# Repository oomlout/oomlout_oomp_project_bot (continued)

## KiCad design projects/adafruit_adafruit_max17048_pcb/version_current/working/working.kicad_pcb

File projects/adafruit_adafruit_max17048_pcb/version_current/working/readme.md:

# OOMP Project  
## Adafruit-MAX17048-PCB  by adafruit  
  
oomp key: oomp_projects_flat_adafruit_adafruit_max17048_pcb  
(snippet of original readme)  
  
-- Adafruit MAX17048 LiPoly / LiIon Fuel Gauge and Battery Monitor PCB  
  
<a href="http://www.adafruit.com/products/5580"><br/>  
Click here to purchase one from the Adafruit shop</a>  
  
PCB files for the Adafruit MAX17048 LiPoly / LiIon Fuel Gauge and Battery Monitor.   
  
Format is EagleCAD schematic and board layout  
* https://www.adafruit.com/product/5580  
  
--- Description  
  
Low cost Lithium Polymer batteries have revolutionized electronics - they're thin, they're light, they can be regulated down to 3.3V and they're easy to charge. On your phone, there's a little image of a battery cell that tells you the percentage of charge - so you know when you absolutely need to plug it in and when you can stay untethered.  
  
The Adafruit MAX17048 LiPoly / LiIon Fuel Gauge and Battery Monitor does the same thing. Connect it to your Lipoly or LiIon battery and it will let you know the voltage of the cell, it does the annoying math of decoding the non-linear voltage to get you a valid percentage as well!  
  
Since this nice chip is I2C, it works with any and all microcontroller or microcomputer boards, from the Arduino UNO up to the Raspberry Pi. And you don't have to worry about logic level, as the gauge runs with 3.3V or 5.0V power and logic equally fine.  
  
To use, connect a 1S 3.7-4.2V Lithium Ion or Polymer battery to one of the JST 2 PH ports (either one). Then use the included JST PH jumper cable to connect to your boost converter, Feather, whatev  
  full source readme at [readme_src.md](readme_src.md)  
  
source repo at: [https://github.com/adafruit/Adafruit-MAX17048-PCB](https://github.com/adafruit/Adafruit-MAX17048-PCB)  
## Board  

## Schematic  

[schematic pdf](working_schematic.pdf)  
## Images

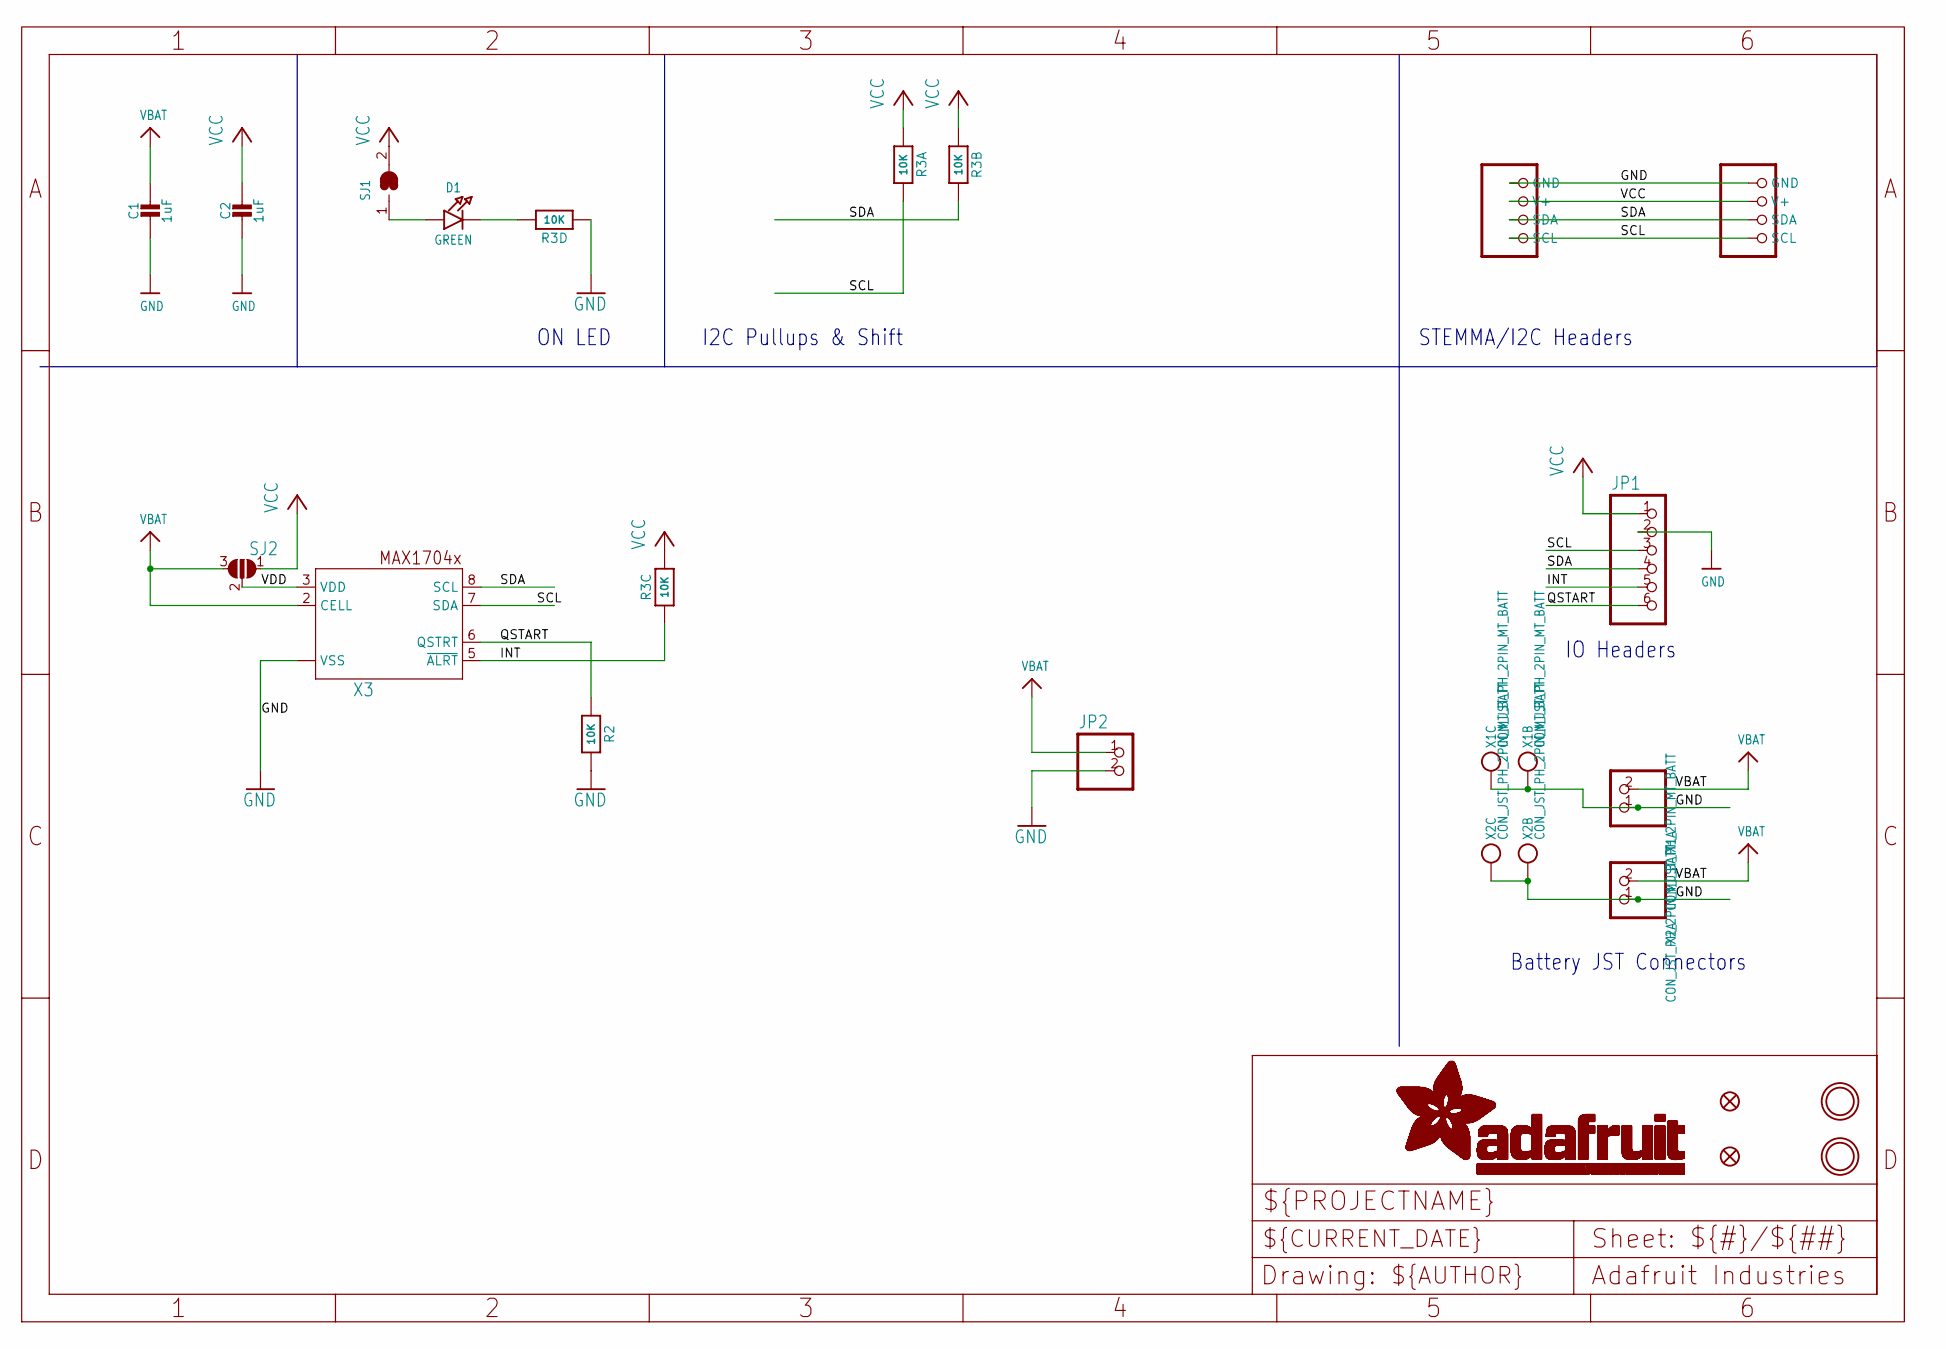
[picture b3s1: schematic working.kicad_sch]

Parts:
C1, C2: 1uF; 0603-NO
CONN3, CONN4: STEMMA_I2C_QT; JST_SH4
D1: GREEN; CHIPLED_0603_NOOUTLINE
FID3, FID4: FIDUCIAL_1MM
JP1: HEADER-1X670MIL; 1X06_ROUND_70
JP2: HEADER-1X2ROUND; 1X02_ROUND
R2: 10K; 0603-NO
R3: 10K; RESPACK_4X0603
SJ1: SOLDERJUMPERCLOSED; SOLDERJUMPER_CLOSEDWIRE
SJ2: SOLDERJUMPER_2WAY; SOLDERJUMPER_2WAY_OPEN_NOPASTE
U$19, U$21: MOUNTINGHOLE2.5; MOUNTINGHOLE_2.5_PLATED
X1, X2: CON_JST_PH_2PIN_MT_BATT; JSTPH2_BATT
X3: MAX17048/T; TDFN8_2X2MM

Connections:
GND: C1.2, C2.2, CONN3.1 (GND), CONN4.1 (GND), JP1.2, JP2.2, R2.2, R3.4 (1), X1.1, X1.NC1, X1.NC2, X2.1, X2.NC1, X2.NC2, X3.1 (VSS), X3.4 (VSS), X3.THERMAL (VSS)
INT: JP1.5, R3.3 (1), X3.5 (~ALRT)
unnamed: D1.C, R3.5 (2)
unnamed: D1.A, SJ1.1
QSTART: JP1.6, R2.1, X3.6 (QSTRT)
SCL: CONN3.4 (SCL), CONN4.4 (SCL), JP1.3, R3.8 (2), X3.7 (SDA)
SDA: CONN3.3 (SDA), CONN4.3 (SDA), JP1.4, R3.7 (2), X3.8 (SCL)
VBAT: C1.1, JP2.1, SJ2.3, X1.2, X2.2, X3.2 (CELL)
VCC: C2.1, CONN3.2 (V+), CONN4.2 (V+), JP1.1, R3.1, R3.2 (1), R3.6 (2), SJ1.2, SJ2.1
VDD: SJ2.2, X3.3 (VDD)

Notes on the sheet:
I2C Pullups & Shift
ON LED
IO Headers
STEMMA/I2C Headers
Battery JST Connectors

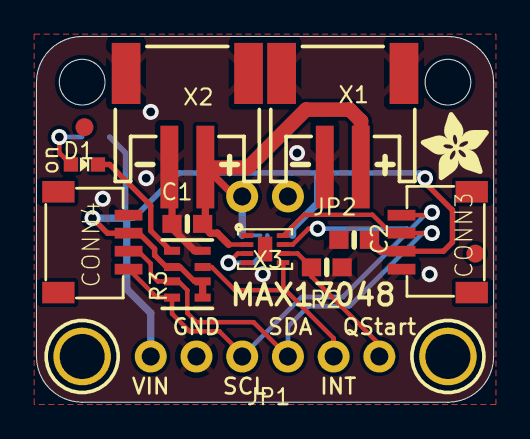
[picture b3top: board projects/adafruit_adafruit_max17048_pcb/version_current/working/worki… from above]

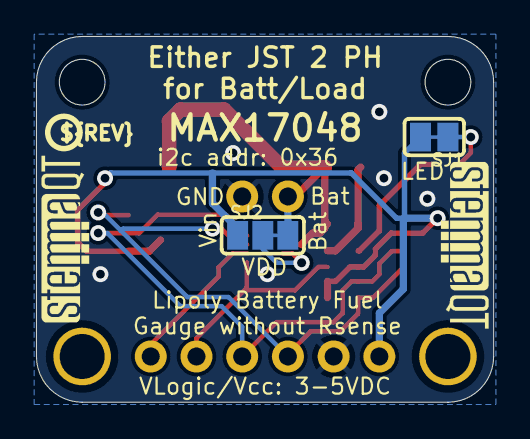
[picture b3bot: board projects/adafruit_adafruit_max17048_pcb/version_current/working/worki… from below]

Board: 2 copper layers, 25.4 x 20.3 mm, 24 parts (5 on the bottom side), 10 nets.

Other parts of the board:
@HOLE0, @HOLE1: (no value)
U$22: ADAFRUIT_3.5MM
U$25: PCBFEAT-REV-040
U$30, U$31: STEMMAQT

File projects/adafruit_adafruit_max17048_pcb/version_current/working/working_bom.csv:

Row,Description,Part,References,Value,Footprint,Quantity Per PCB,Status,Datasheet
1,,CAP_CERAMIC0603_NO,C1 C2,1uF,0603-NO,2, ,
2,,STEMMA_I2C_QT,CONN3 CONN4,STEMMA_I2C_QT,JST_SH4,2, ,
3,,LED0603_NOOUTLINE,D1,GREEN,CHIPLED_0603_NOOUTLINE,1, ,
4,,HEADER-1X2ROUND,JP2,HEADER-1X2ROUND,1X02_ROUND,1, ,
5,,HEADER-1X670MIL,JP1,HEADER-1X670MIL,1X06_ROUND_70,1, ,
6,,RESISTOR_0603_NOOUT,R2,10K,0603-NO,1, ,
7,,RESISTOR_4PACK,R3,10K,RESPACK_4X0603,1, ,
8,,CON_JST_PH_2PIN_MT_BATT,X1 X2,CON_JST_PH_2PIN_MT_BATT,JSTPH2_BATT,2, ,
9,,MAX17048/T,X3,MAX17048/T,TDFN8_2X2MM,1, ,





Project info:
Schematic:,working
Variant:,default
Revision:,
Date:,2023-08-03_17-21-22
KiCad Version:,7.0.6-7.0.6~ubuntu22.04.1
Statistics:
Component Groups:,9
Component Count:,12 (0 SMD/ 0 THT)
Fitted Components:,12 (0 SMD/ 0 THT)
Number of PCBs:,1
Total Components:,12

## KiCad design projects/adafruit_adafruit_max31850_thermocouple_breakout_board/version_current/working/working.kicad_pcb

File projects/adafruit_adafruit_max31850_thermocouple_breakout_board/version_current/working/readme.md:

# OOMP Project  
## Adafruit-MAX31850-thermocouple-breakout-board  by adafruit  
  
oomp key: oomp_projects_flat_adafruit_adafruit_max31850_thermocouple_breakout_board  
(snippet of original readme)  
  
- PCB files for Adafruit MAX31850 1-Wire Thermocouple Breakout Board  
  
<a href="http://www.adafruit.com/products/1727"><br/>Click here to purchase one from the Adafruit shop</a>  
  
Thermocouples are very sensitive, requiring a good amplifier with a cold-compensation reference. [So far we've carried the very nice MAX31855 which is an SPI interface thermocouple amplifier](https://www.adafruit.com/products/269). The '855 is great but if you have a lot of thermocouples to measure it isn't terribly easy to use. That's why we are also carrying the new '850 model from Maxim - it's a "1-Wire" thermocouple amp which can have any number of breakouts on a single shared I/O line.  
  
The MAX31850K does everything for you, and can be easily interfaced with any microcontroller that has 1-Wire support. This breakout board has the chip itself, a 3.3V regulator with 10uF bypass capacitors all assembled and tested. This board can be used with 'parasitic power' - where the power is on the data line - or with 'local power' where the power for the converter comes in on the Vin Pin.  
  
Please note: this board does not have level shifting on the 3V Data line - we did this on purpose so that it can be used in parasitic mode. The data line must be level shifted to [3V - our 4-channel shifter works wonderfully for level shifting 1-Wire](http://www.adafruit.com/products/757) and you only need one at the '1-Wire host' for all thermocouples on the shared data li  
  full source readme at [readme_src.md](readme_src.md)  
  
source repo at: [https://github.com/adafruit/Adafruit-MAX31850-thermocouple-breakout-board](https://github.com/adafruit/Adafruit-MAX31850-thermocouple-breakout-board)  
## Board  

## Schematic  

[schematic pdf](working_schematic.pdf)  
## Images

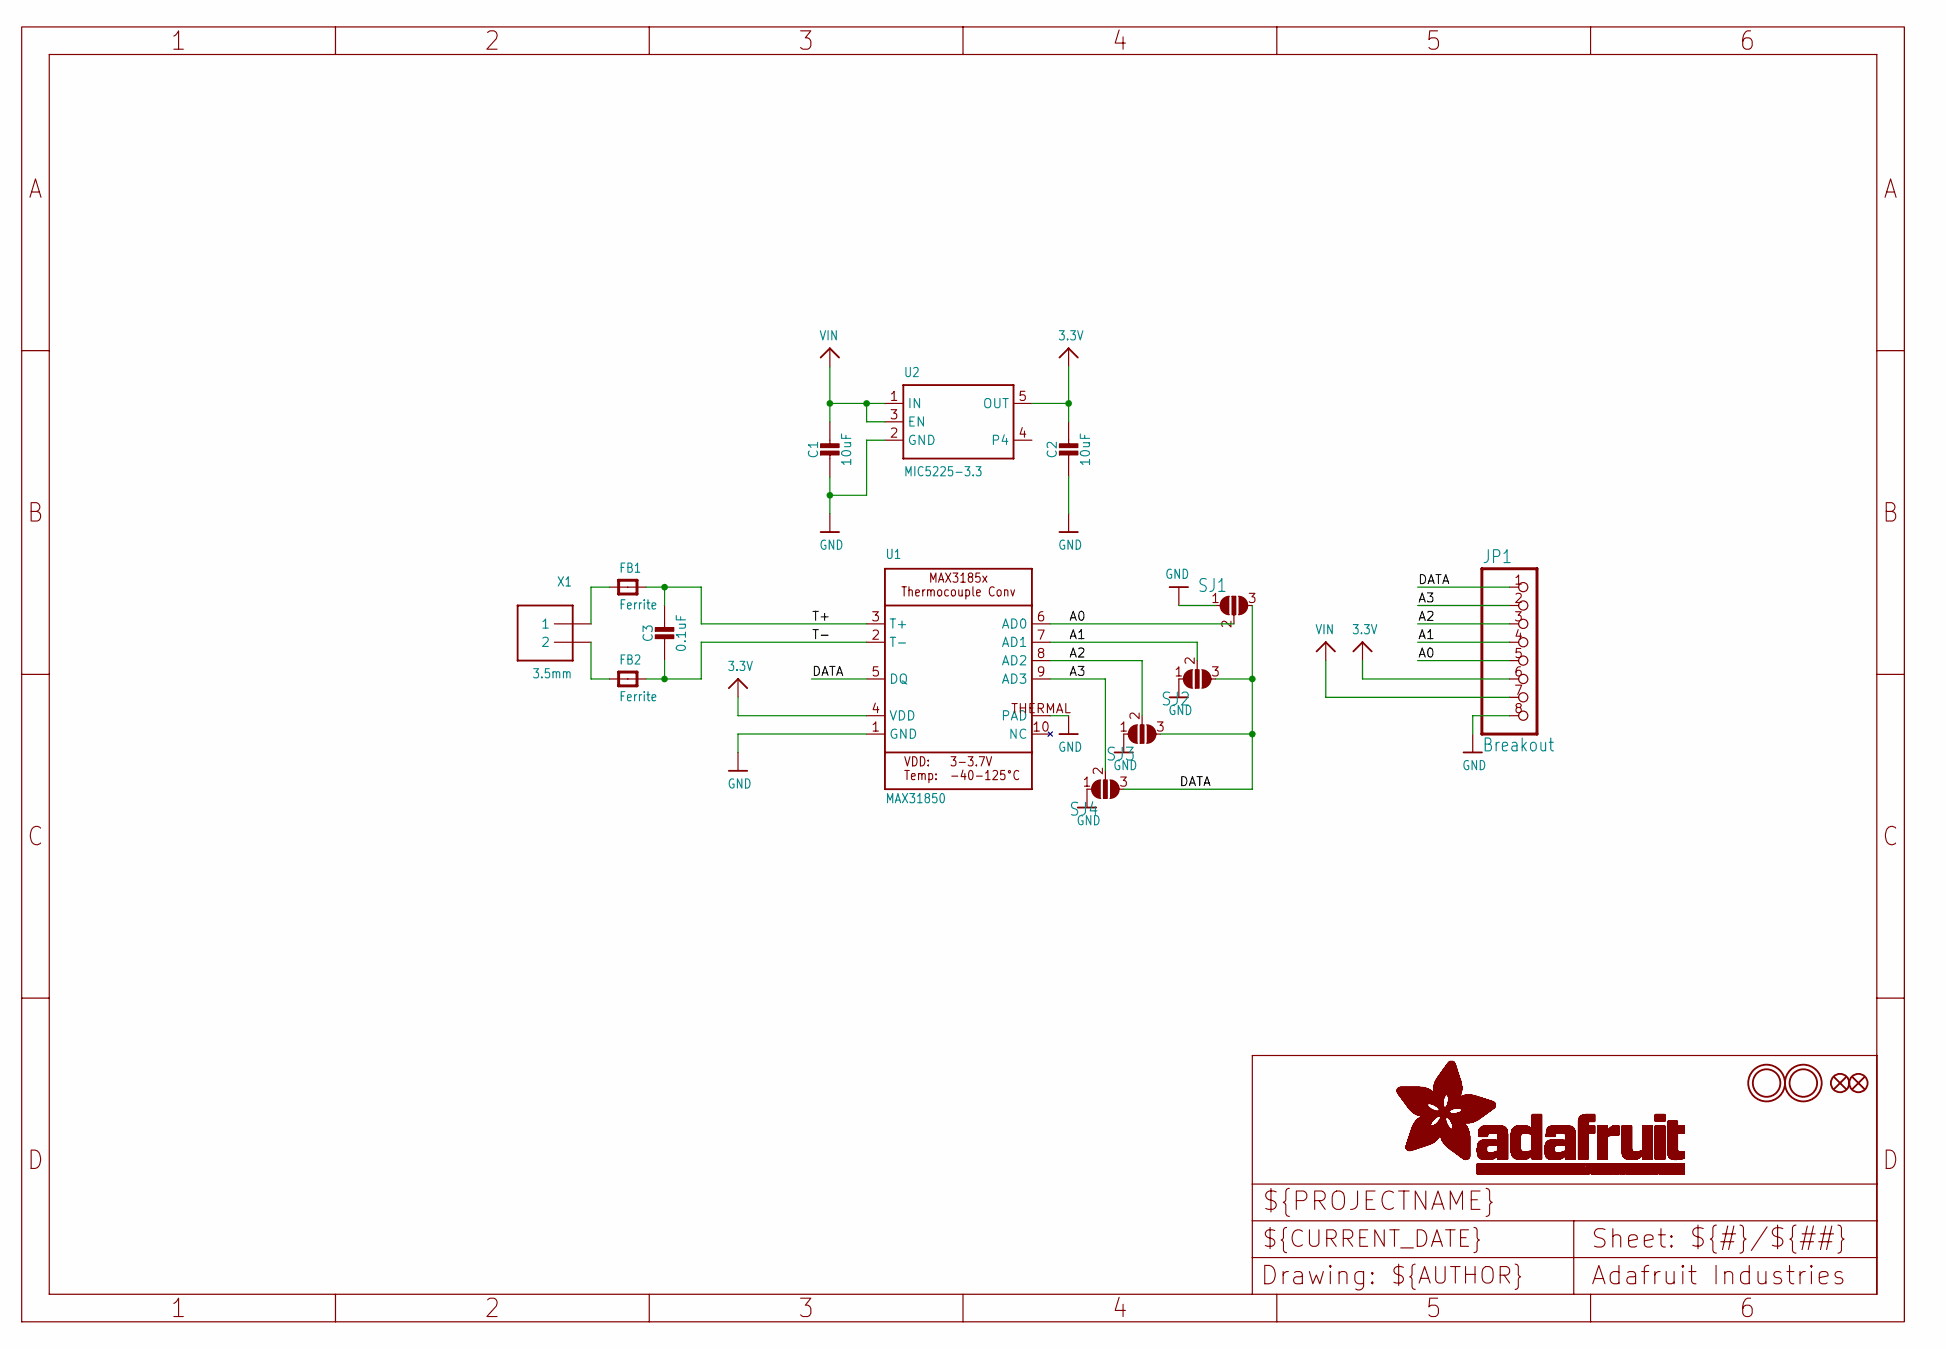
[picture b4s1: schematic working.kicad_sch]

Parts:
C1, C2: 10uF; 0805-NO
C3: 0.1uF; 0805-NO
FB1, FB2: Ferrite; 0805
FID1, FID2: FIDUCIAL""; FIDUCIAL_1MM
JP1: Breakout; 1X08_ROUND_70
SJ1, SJ2, SJ3, SJ4: SOLDERJUMPER_2WAY; SOLDERJUMPER_2WAY_OPEN_NOPASTE
U1: MAX31850; TDFN10_3X4MM
U2: MIC5225-3.3; SOT23-5
U$8, U$9: MOUNTINGHOLE2.5; MOUNTINGHOLE_2.5_PLATED
X1: 3.5mm; TERMBLOCK_1X2-3.5MM

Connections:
3.3V: C2.1, JP1.6, U1.4 (VDD), U2.5 (OUT)
A0: JP1.5, SJ1.2, U1.6 (AD0)
A1: JP1.4, SJ2.2, U1.7 (AD1)
A2: JP1.3, SJ3.2, U1.8 (AD2)
A3: JP1.2, SJ4.2, U1.9 (AD3)
DATA: JP1.1, SJ1.3, SJ2.3, SJ3.3, SJ4.3, U1.5 (DQ)
GND: C1.2, C2.2, JP1.8, SJ1.1, SJ2.1, SJ3.1, SJ4.1, U1.1 (GND), U1.THERMAL (PAD), U2.2 (GND)
unnamed: FB1.1, X1.1
unnamed: FB2.1, X1.2
T+: C3.1, FB1.2, U1.3 (T+)
T-: C3.2, FB2.2, U1.2 (T-)
VIN: C1.1, JP1.7, U2.1 (IN), U2.3 (EN)

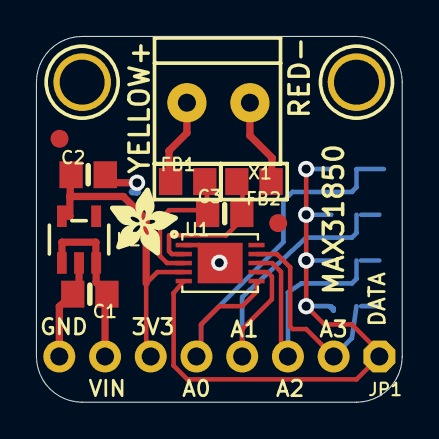
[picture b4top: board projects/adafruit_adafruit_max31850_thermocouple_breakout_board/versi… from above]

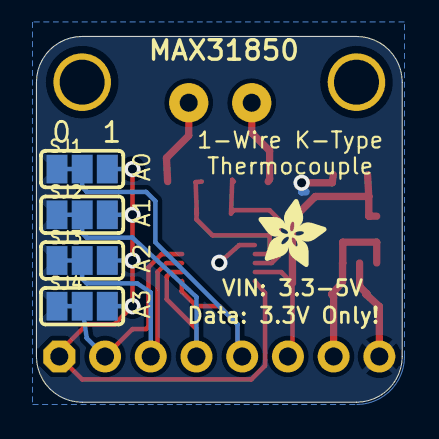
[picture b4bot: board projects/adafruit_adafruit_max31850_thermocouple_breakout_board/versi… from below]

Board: 2 copper layers, 20.3 x 20.3 mm, 19 parts (5 on the bottom side), 12 nets.

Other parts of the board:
U$18, U$19: ADAFRUIT_3.5MM

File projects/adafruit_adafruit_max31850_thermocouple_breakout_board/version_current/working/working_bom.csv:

Row,Description,Part,References,Value,Footprint,Quantity Per PCB,Status,Datasheet
1,,CAP_CERAMIC0805-NOOUTLINE,C3,0.1uF,0805-NO,1, ,
2,,CAP_CERAMIC0805-NOOUTLINE,C1 C2,10uF,0805-NO,2, ,
3,,FERRITE0805,FB1 FB2,Ferrite,0805,2, ,
4,,HEADER-1X870MIL,JP1,Breakout,1X08_ROUND_70,1, ,
5,,MAX3185X,U1,MAX31850,TDFN10_3X4MM,1, ,
6,,VREG_SOT23-5,U2,MIC5225-3.3,SOT23-5,1, ,
7,,TERMBLOCK_1X2,X1,3.5mm,TERMBLOCK_1X2-3.5MM,1, ,





Project info:
Schematic:,working
Variant:,default
Revision:,
Date:,2023-08-03_17-21-22
KiCad Version:,7.0.6-7.0.6~ubuntu22.04.1
Statistics:
Component Groups:,7
Component Count:,9 (0 SMD/ 0 THT)
Fitted Components:,9 (0 SMD/ 0 THT)
Number of PCBs:,1
Total Components:,9

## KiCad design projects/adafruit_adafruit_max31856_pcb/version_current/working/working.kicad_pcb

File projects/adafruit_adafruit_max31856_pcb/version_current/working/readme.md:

# Adafruit-MAX31856-PCB by adafruit  
This is a harvested standardized copy of a project from github.  
The original project can be found at:  
https://github.com/adafruit/Adafruit-MAX31856-PCB  
Please consult that link for additional, details, files, and license information.  
Note: It was auto harvested and if the original repo had more than one board file or anything out of the ordinary the files here are likely not representative.

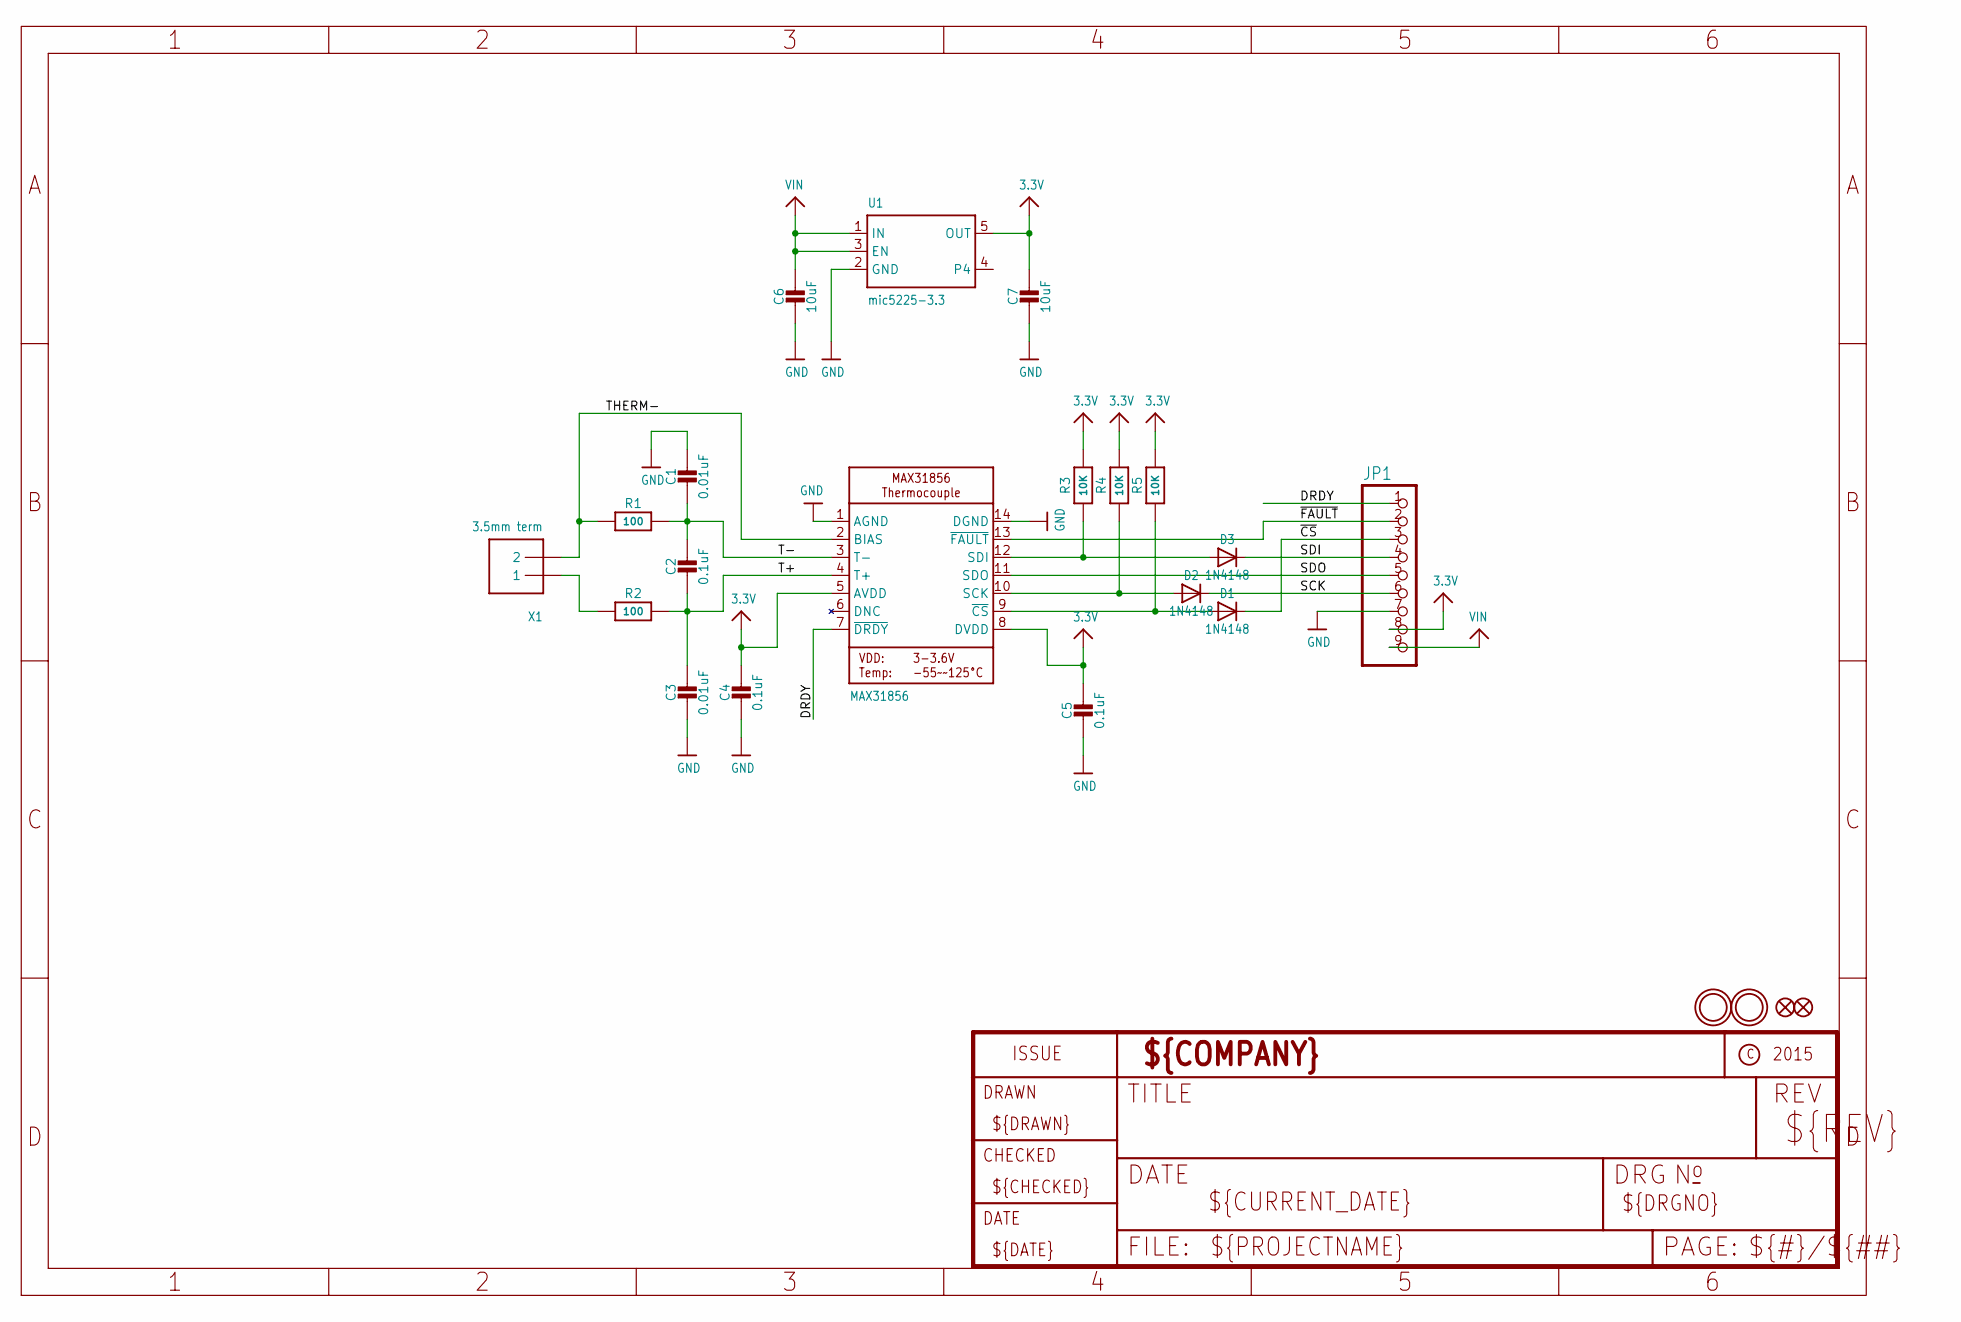
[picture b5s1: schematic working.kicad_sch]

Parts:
C1: 0.01uF; 0805_10MGAP
C2, C4, C5: 0.1uF; 0805-NO
C3: 0.01uF; 0805-NO
C6, C7: 10uF; 0805-NO
D1, D2, D3: 1N4148; SOD-323
FID1, FID2: FIDUCIAL""; FIDUCIAL_1MM
JP1: HEADER-1X970MIL; 1X09_ROUND_70
R1, R2: 100; 0805-NO
R3, R4, R5: 10K; 0805-NO
U1: mic5225-3.3; SOT23-5
U2: MAX31856; TSSOP14
U$13, U$14: MOUNTINGHOLE2.5; MOUNTINGHOLE_2.5_PLATED
X1: 3.5mm term; TERMBLOCK_1X2-3.5MM

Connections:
3.3V: C4.1, C5.1, C7.1, JP1.8, R3.2, R4.2, R5.2, U1.5 (OUT), U2.5 (AVDD), U2.8 (DVDD)
DRDY: JP1.1, U2.7 (~DRDY)
GND: C1.1, C3.2, C4.2, C5.2, C6.2, C7.2, JP1.7, U1.2 (GND), U2.1 (AGND), U2.14 (DGND)
SCK: D2.C, JP1.6
SCK_3V: D2.A, R4.1, U2.10 (SCK)
SDI: D3.C, JP1.4
SDO: JP1.5, U2.11 (SDO)
SDO_3V: D3.A, R3.1, U2.12 (SDI)
T+: C2.2, C3.1, R2.2, U2.4 (T+)
T-: C1.2, C2.1, R1.2, U2.3 (T-)
THERM+: R2.1, X1.1
THERM-: R1.1, U2.2 (BIAS), X1.2
VIN: C6.1, JP1.9, U1.1 (IN), U1.3 (EN)
~CS_3V: D1.A, R5.1, U2.9 (~CS)
~CS: D1.C, JP1.3
~FAULT: JP1.2, U2.13 (~FAULT)

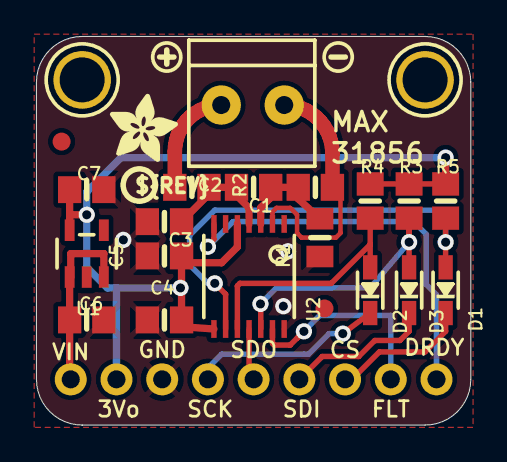
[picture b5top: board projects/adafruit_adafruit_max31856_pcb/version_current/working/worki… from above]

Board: 2 copper layers, 24.1 x 21.6 mm, 28 parts (1 on the bottom side), 16 nets.

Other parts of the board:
U$1: PCBFEAT-REV-040
U$23: SYMBOL_PLUS
U$24: SYMBOL_MINUS
U$25: ADAFRUIT_3.5MM
U$26: ADAFRUIT_TEXT_20MM

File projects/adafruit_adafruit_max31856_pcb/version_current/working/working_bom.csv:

Row,Description,Part,References,Value,Footprint,Quantity Per PCB,Status,Datasheet
1,,CAP_CERAMIC0805_10MGAP,C1,0.01uF,0805_10MGAP,1, ,
2,,CAP_CERAMIC0805-NOOUTLINE,C3,0.01uF,0805-NO,1, ,
3,,CAP_CERAMIC0805-NOOUTLINE,C2 C4 C5,0.1uF,0805-NO,3, ,
4,,CAP_CERAMIC0805-NOOUTLINE,C6 C7,10uF,0805-NO,2, ,
5,,DIODESOD-323,D1 D2 D3,1N4148,SOD-323,3, ,
6,,HEADER-1X970MIL,JP1,HEADER-1X970MIL,1X09_ROUND_70,1, ,
7,,RESISTOR0805_NOOUTLINE,R1 R2,100,0805-NO,2, ,
8,,RESISTOR0805_NOOUTLINE,R3 R4 R5,10K,0805-NO,3, ,
9,,MAX31856,U2,MAX31856,TSSOP14,1, ,
10,,VREG_SOT23-5,U1,mic5225-3.3,SOT23-5,1, ,
11,,TERMBLOCK_1X2,X1,3.5mm term,TERMBLOCK_1X2-3.5MM,1, ,





Project info:
Schematic:,working
Variant:,default
Revision:,
Date:,2023-08-03_17-21-22
KiCad Version:,7.0.6-7.0.6~ubuntu22.04.1
Statistics:
Component Groups:,11
Component Count:,19 (0 SMD/ 0 THT)
Fitted Components:,19 (0 SMD/ 0 THT)
Number of PCBs:,1
Total Components:,19

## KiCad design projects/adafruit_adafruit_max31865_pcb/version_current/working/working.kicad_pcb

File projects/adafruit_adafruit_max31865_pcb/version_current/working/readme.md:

# OOMP Project  
## Adafruit-MAX31865-PCB  by adafruit  
  
oomp key: oomp_projects_flat_adafruit_adafruit_max31865_pcb  
(snippet of original readme)  
  
-- Adafruit MAX31865 PCB  
  
<a href="http://www.adafruit.com/products/3328"><br/>  
Click here to purchase one from the Adafruit shop</a>  
  
PCB files for the Adafruit MAX31865 RTD Sensor Breakout. Format is EagleCAD schematic and board layout  
* https://www.adafruit.com/product/3328  
  
--- Description  
  
For precision temperature sensing, nothing beats a Platinum RTD. Resistance temperature detectors (RTDs) are temperature sensors that contain a resistor that changes resistance value as its temperature changes, basically a kind of thermistor. In this sensor, the resistor is actually a small strip of Platinum with a resistance of 100 ohms at 0°C, thus the name PT100. Compared to most NTC/PTC thermistors, the PT type of RTD is much most stable and precise (but also more expensive) PT100's have been used for many years to measure temperature in laboratory and industrial processes, and have developed a reputation for accuracy (better than thermocouples), repeatability, and stability.   
  
However, to get that precision and accuracy out of your PT100 RTD you must use an amplifier that is designed to read the low resistance. Better yet, have an amplifier that can automatically adjust and compensate for the resistance of the connecting wires. If you're looking for a great RTD sensor, today is your lucky day because we have a lovely Adafruit RTD Sensor Amplifier with the MAX31865 breakout for use with any 2, 3 or 4 wire PT100 RTD!  
  
--- License  
  
A  
  full source readme at [readme_src.md](readme_src.md)  
  
source repo at: [https://github.com/adafruit/Adafruit-MAX31865-PCB](https://github.com/adafruit/Adafruit-MAX31865-PCB)  
## Board  

## Schematic  

[schematic pdf](working_schematic.pdf)  
## Images

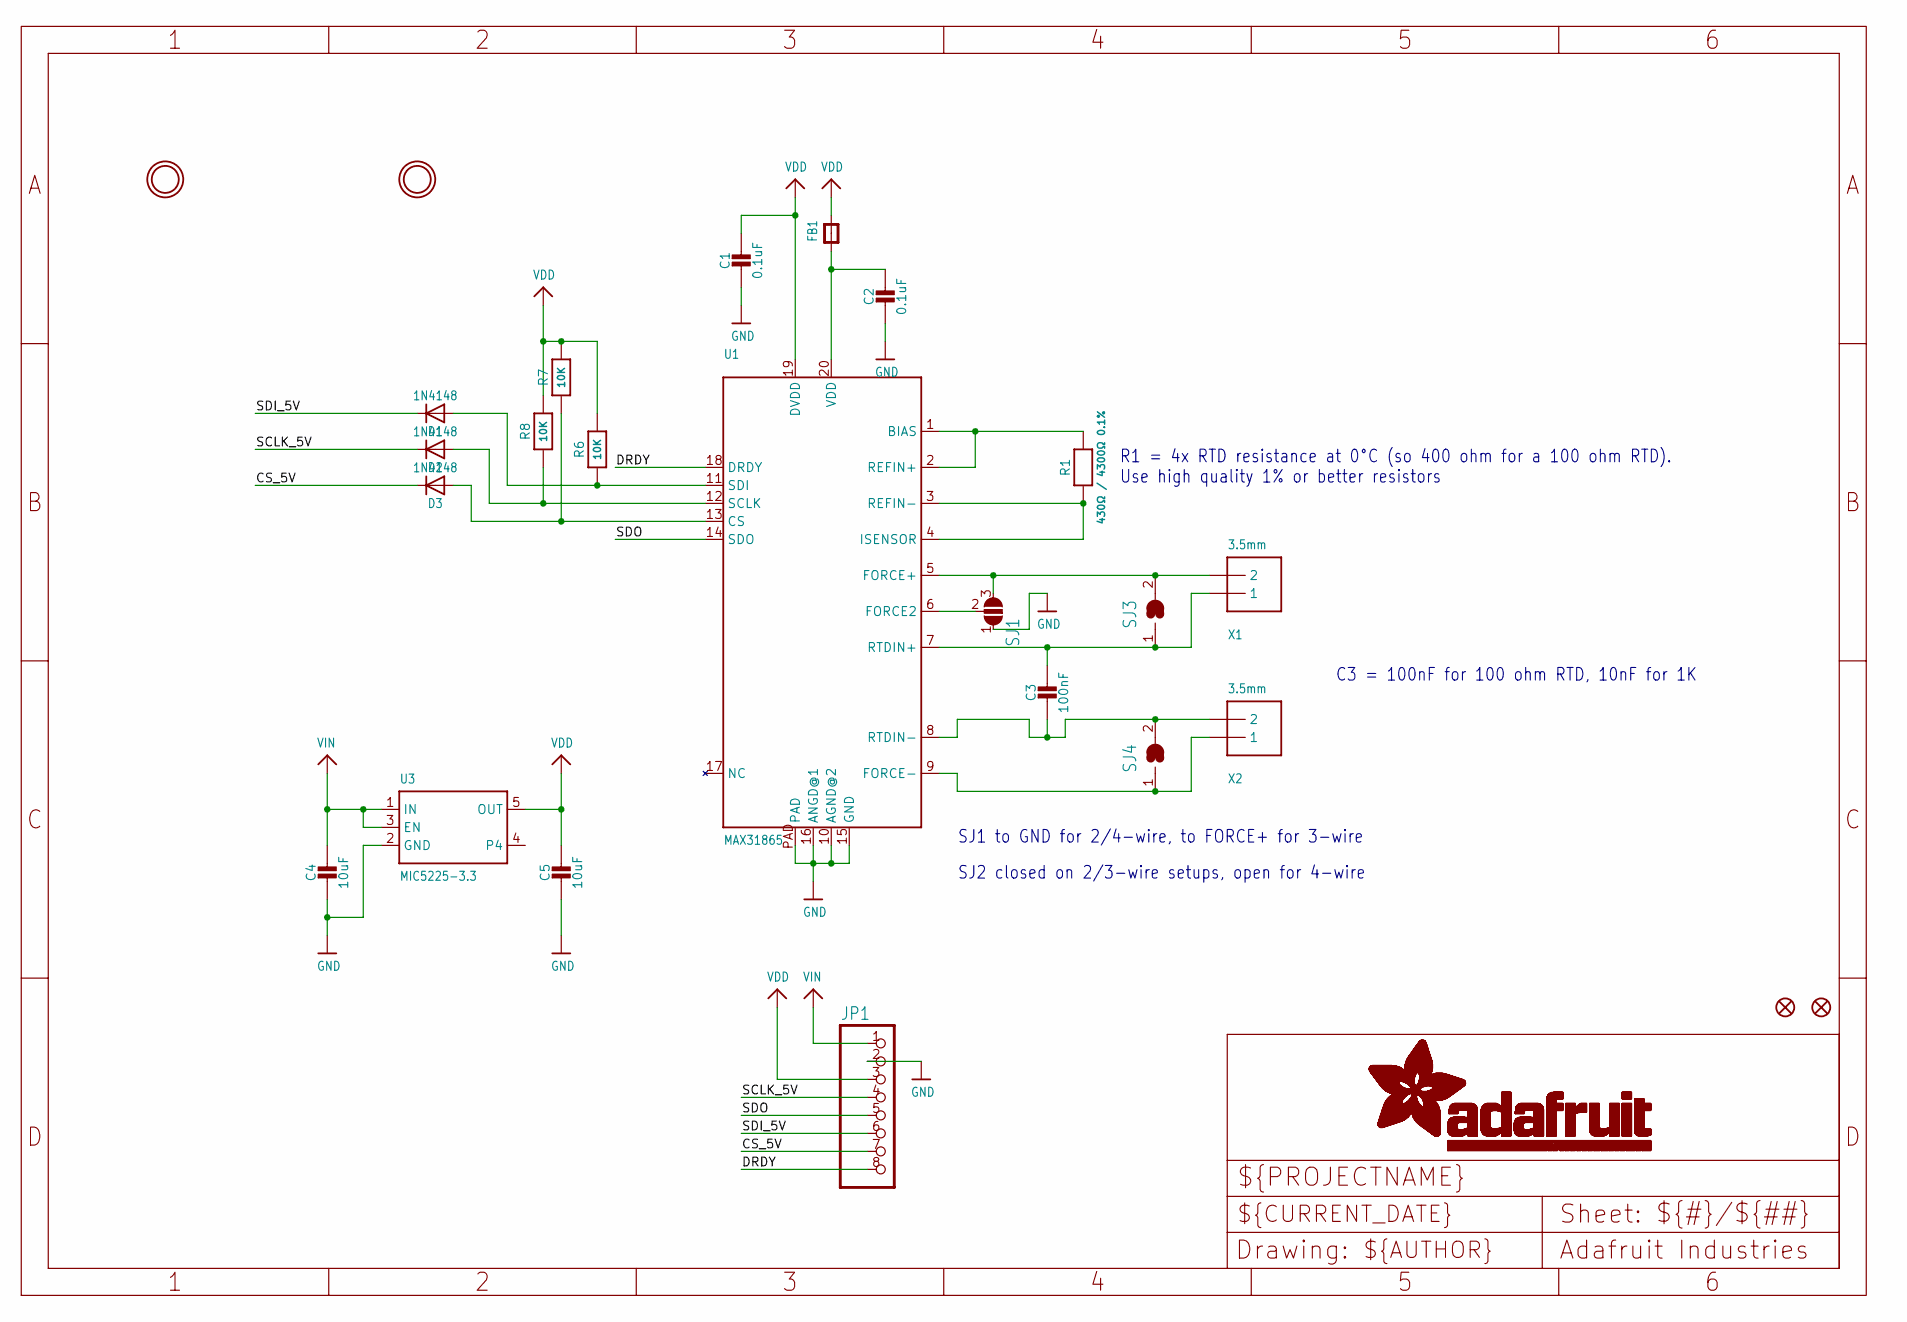
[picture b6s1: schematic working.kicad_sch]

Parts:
C1, C2: 0.1uF; 0805-NO
C3: 100nF; 0805-NO
C4, C5: 10uF; 0805-NO
D1, D2, D3: 1N4148; SOD-323
FB1: FERRITE-0805NO; 0805-NO
FID1, FID2: FIDUCIAL""; FIDUCIAL_1MM
JP1: HEADER-1X870MIL; 1X08_ROUND_70
R1: 430Ω / 4300Ω 0.1%; 0805-NO
R6, R7, R8: 10K; 0805-NO
SJ1: SOLDERJUMPER_2WAY; SOLDERJUMPER_2WAY_OPEN_NOPASTE
SJ3, SJ4: SOLDERJUMPER; SOLDERJUMPER_ARROW_NOPASTE
U1: MAX31865; QFN20_4MM_0.65MM
U3: MIC5225-3.3; SOT23-5
U$18, U$19: MOUNTINGHOLE2.5; MOUNTINGHOLE_2.5_PLATED
X1, X2: 3.5mm; TERMBLOCK_1X2-3.5MM

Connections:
CS_5V: D3.C, JP1.7
DRDY: JP1.8, U1.18 (DRDY)
FORCE+: SJ1.3, SJ3.2, U1.5 (FORCE+), X1.2
FORCE-: SJ4.1, U1.9 (FORCE-), X2.1
GND: C1.2, C2.2, C4.2, C5.2, JP1.2, SJ1.1, U1.10 (AGND@2), U1.15 (GND), U1.16 (ANGD@1), U1.PAD, U3.2 (GND)
unnamed: R1.1, U1.3 (REFIN-), U1.4 (ISENSOR)
unnamed: R1.2, U1.1 (BIAS), U1.2 (REFIN+)
unnamed: C2.1, FB1.1, U1.20 (VDD)
unnamed: SJ1.2, U1.6 (FORCE2)
unnamed: D3.A, R7.1, U1.13 (CS)
unnamed: D2.A, R8.1, U1.12 (SCLK)
unnamed: D1.A, R6.1, U1.11 (SDI)
RTDIN+: C3.1, SJ3.1, U1.7 (RTDIN+), X1.1
RTDIN-: C3.2, SJ4.2, U1.8 (RTDIN-), X2.2
SCLK_5V: D2.C, JP1.4
SDI_5V: D1.C, JP1.6
SDO: JP1.5, U1.14 (SDO)
VDD: C1.1, C5.1, FB1.2, JP1.3, R6.2, R7.2, R8.2, U1.19 (DVDD), U3.5 (OUT)
VIN: C4.1, JP1.1, U3.1 (IN), U3.3 (EN)

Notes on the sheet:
SJ2 closed on 2/3-wire setups, open for 4-wire
SJ1 to GND for 2/4-wire, to FORCE+ for 3-wire
R1 = 4x RTD resistance at 0°C (so 400 ohm for a 100 ohm RTD). Use high quality 1% or better resistors
C3 = 100nF for 100 ohm RTD, 10nF for 1K

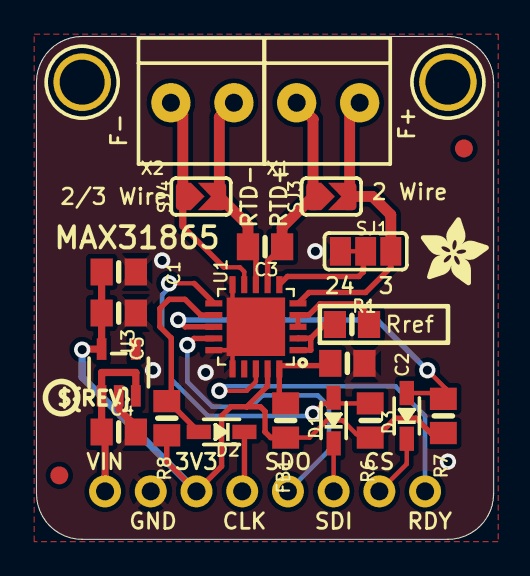
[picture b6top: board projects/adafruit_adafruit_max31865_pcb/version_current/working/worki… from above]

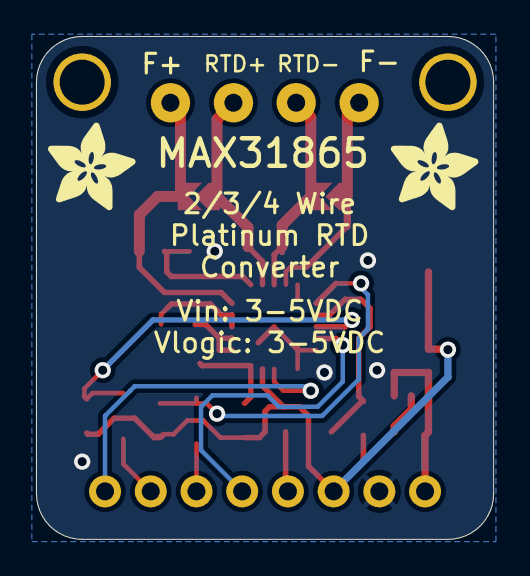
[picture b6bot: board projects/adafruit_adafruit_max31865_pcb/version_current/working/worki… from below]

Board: 2 copper layers, 25.4 x 27.9 mm, 29 parts (2 on the bottom side), 19 nets.

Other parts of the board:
U$8: PCBFEAT-REV-040
U$16: ADAFRUIT_3.5MM
U$20, U$21: ADAFRUIT_5MM

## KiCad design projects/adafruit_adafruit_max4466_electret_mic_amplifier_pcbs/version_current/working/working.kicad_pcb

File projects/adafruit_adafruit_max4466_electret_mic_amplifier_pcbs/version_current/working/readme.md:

# OOMP Project  
## Adafruit-MAX4466-Electret-Mic-Amplifier-PCBs  by adafruit  
  
oomp key: oomp_projects_flat_adafruit_adafruit_max4466_electret_mic_amplifier_pcbs  
(snippet of original readme)  
  
- Adafruit MAX4466 Electret Mic Amplifier PCBs  
<a href="http://www.adafruit.com/products/1063"><br/>  
Click here to purchase one from the Adafruit shop</a>  
  
Add an ear to your project with this well-designed electret microphone amplifier. This fully assembled and tested board comes with a 20-20KHz electret microphone soldered on. For the amplification, we use the Maxim MAX4466, an op-amp specifically designed for this delicate task! The amplifier has excellent power supply noise rejection, so this amplifier sounds really good and isn't nearly as noisy or scratchy as other mic amp breakouts we've tried!  
  
This breakout is best used for projects such as voice changers, audio recording/sampling, and audio-reactive projects that use FFT. On the back, we include a small trimmer pot to adjust the gain. You can set the gain from 25x to 125x. That's down to be about 200mVpp (for normal speaking volume about 6" away) which is good for attaching to something that expects 'line level' input without clipping, or up to about 1Vpp, ideal for reading from a microcontroller ADC. The output is rail-to-rail so if the sounds gets loud, the output can go up to 5Vpp!  
  
PCB files for Adafruit MAX4466 Electret Mic Amplifier. The format is EagleCAD schematic and board layout  
  
For more details, check out the product page at https://www.adafruit.com/products/1063  
  
--- License  
  
Adafruit invests time and resources providing this open source design, please   
  full source readme at [readme_src.md](readme_src.md)  
  
source repo at: [https://github.com/adafruit/Adafruit-MAX4466-Electret-Mic-Amplifier-PCBs](https://github.com/adafruit/Adafruit-MAX4466-Electret-Mic-Amplifier-PCBs)  
## Board  

## Schematic  

[schematic pdf](working_schematic.pdf)  
## Images

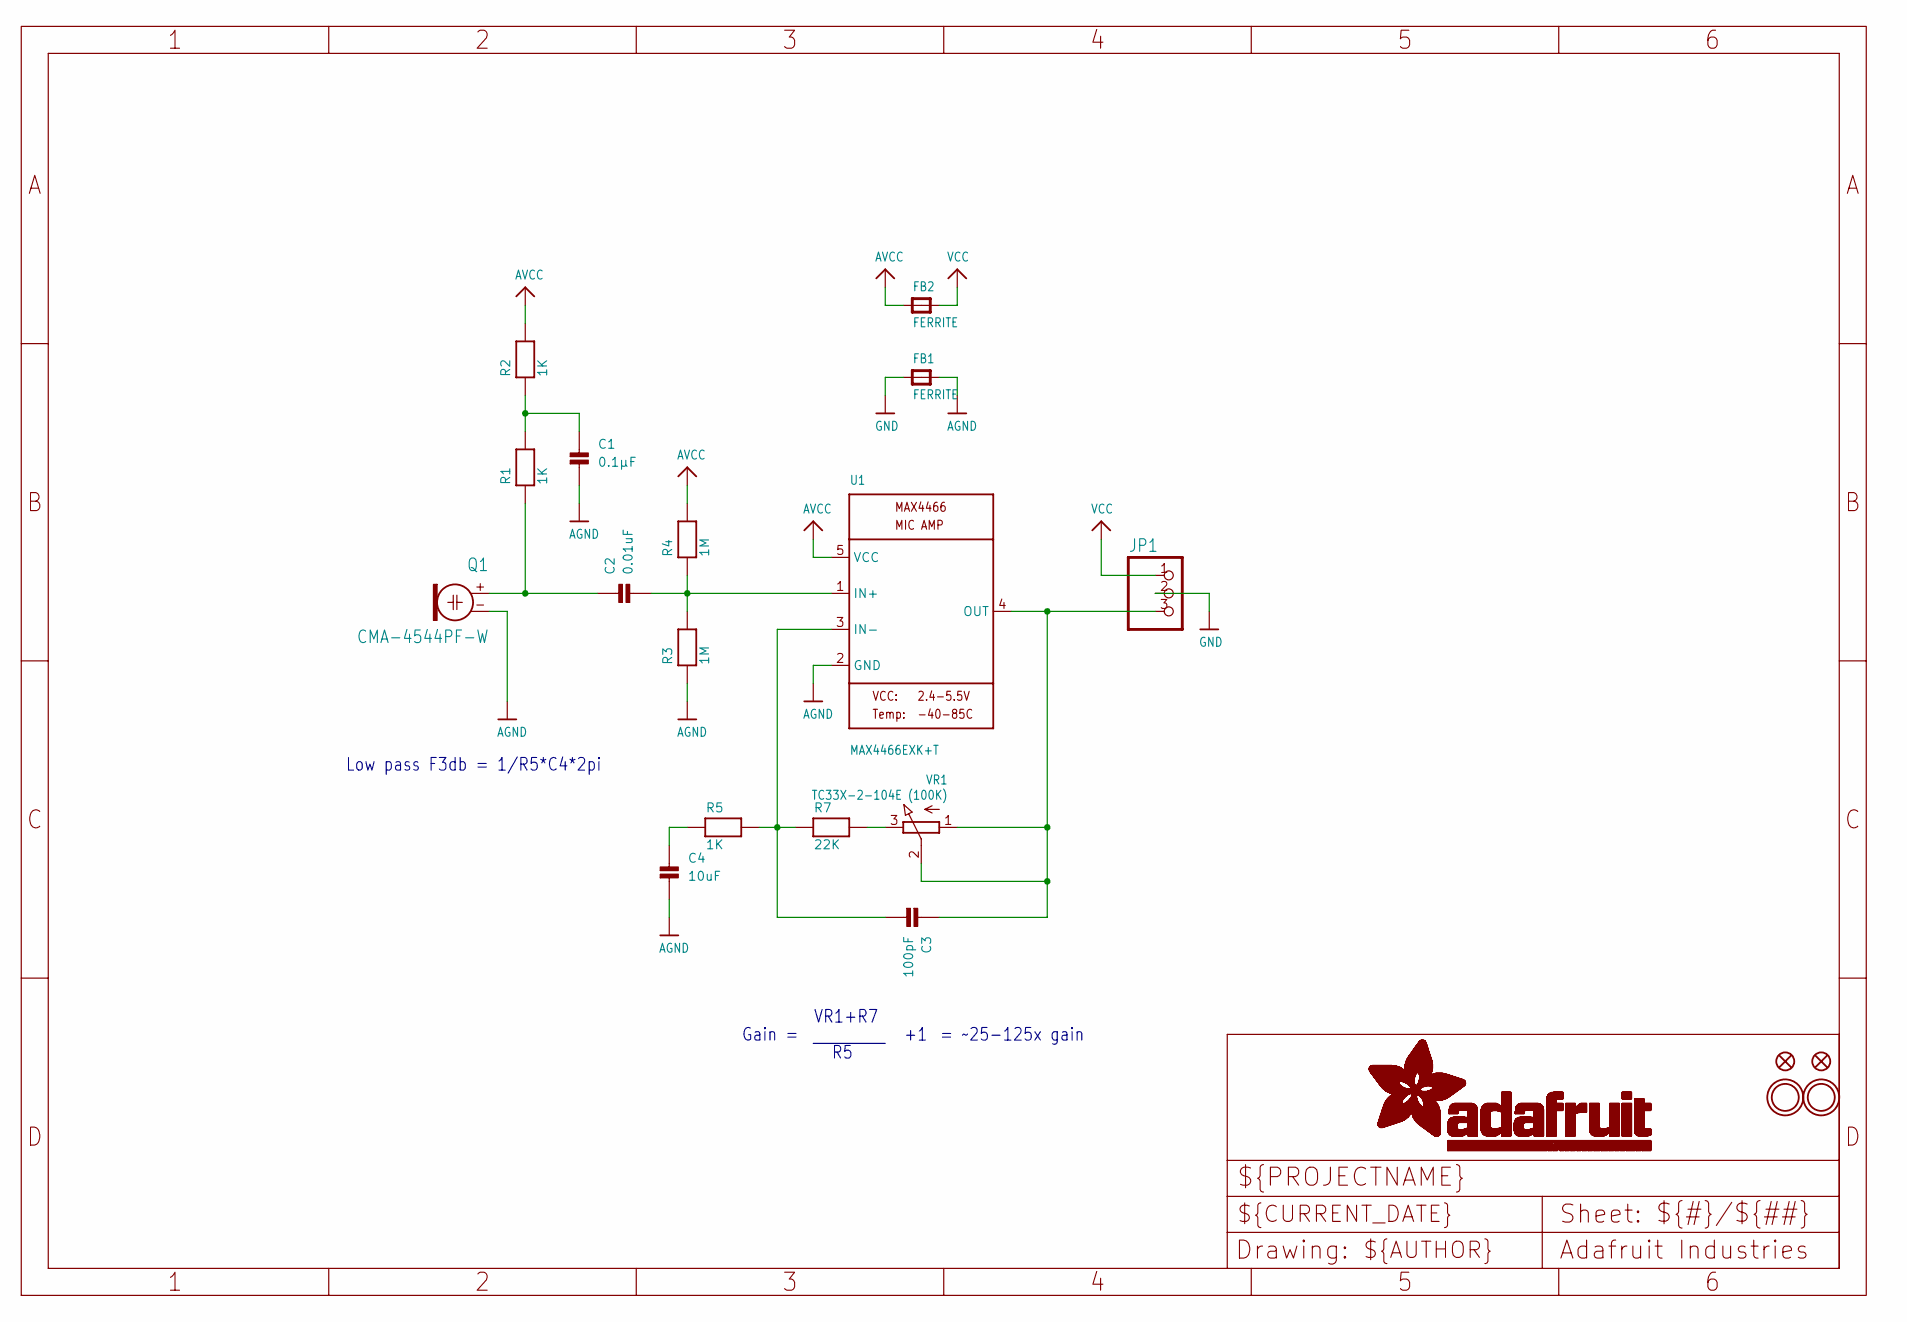
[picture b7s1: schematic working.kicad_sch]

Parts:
C1: 0.1µF; 0805
C2: 0.01uF; 0805
C3: 100pF; 0805
C4: 10uF; 0805
FB1, FB2: FERRITE; 0805
FID1, FID2: FIDUCIAL""; FIDUCIAL_1MM
JP1: HEADER-1X376MIL; 1X03_ROUND_76
Q1: CMA-4544PF-W; ELECTRET_9.7
R1, R2, R5: 1K; 0805
R3, R4: 1M; 0805
R7: 22K; 0805
U1: MAX4466EXK+T; SC70-5
U$11, U$14: MOUNTINGHOLE2.5; MOUNTINGHOLE_2.5_PLATED
VR1: TC33X-2-104E (100K); TRIMPOT_BOURNS_TC33X-2

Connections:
AGND: C1.2, C4.2, FB1.2, Q1.- (1), R3.1, U1.2 (GND)
AVCC: FB2.1, R2.2, R4.2, U1.5 (VCC)
GND: FB1.1, JP1.2
unnamed: C3.2, R5.2, R7.1, U1.3 (IN-)
unnamed: R7.2, VR1.3 (E)
unnamed: C2.1, Q1.+ (2), R1.1
unnamed: C1.1, R1.2, R2.1
unnamed: C2.2, R3.2, R4.1, U1.1 (IN+)
unnamed: C3.1, JP1.3, U1.4 (OUT), VR1.1 (A), VR1.2 (S)
unnamed: C4.1, R5.1
VCC: FB2.2, JP1.1

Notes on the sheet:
Low pass F3db = 1/R5*C4*2pi
VR1+R7
Gain =
= ~25-125x gain
